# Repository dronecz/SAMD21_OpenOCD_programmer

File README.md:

# SAMD21_OpenOCD_programmer

HW/rev_B - working programmer, buttons & OLED display. SWD header untested.

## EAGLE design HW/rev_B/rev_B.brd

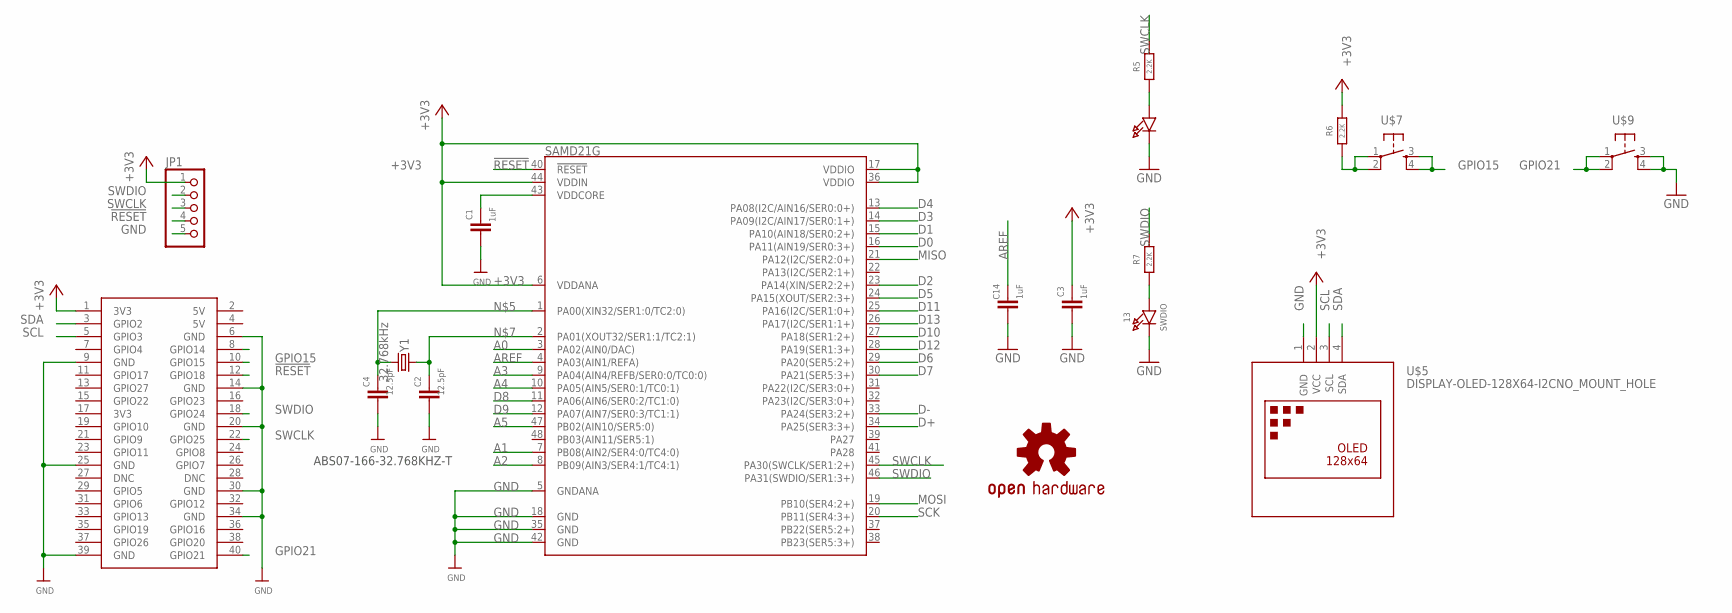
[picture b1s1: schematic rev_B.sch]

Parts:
5: SWCLK; CHIPLED_0805_NOOUTLINE
13: SWDIO; CHIPLED_0805_NOOUTLINE
C1, C3, C14: 1uF; C0805
C2, C4: 12.5pF; C0805
JP1: PINHD-1X5; 1X05
LOGO1: OSHW-LOGOS; OSHW-LOGO-S
R5, R6, R7: 2.2K; R0805
SAMD21G: ATSAMD21G-A; TQFP-48
U$1: RASPBERRY_PI_ZERO
U$5: DISPLAY-OLED-128X64-I2CNO_MOUNT_HOLE; DISPLAY-OLED-128X64-I2C
U$7, U$9: TACTILE_SWITCH_LONG_THT_; TACTILE_SWICTH_THT
Y1: 32.768kHz; CRYSTAL-SMD-3.2X1.5MM

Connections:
!RESET: JP1.4, SAMD21G.40 (!RESET!), U$1.12 (GPIO18)
+3V3: C3.1, JP1.1, R6.1, SAMD21G.6 (VDDANA), SAMD21G.17 (VDDIO), SAMD21G.36 (VDDIO), SAMD21G.44 (VDDIN), U$1.1 (3V3), U$5.2 (VCC)
A0: SAMD21G.3 (PA02(AIN0/DAC))
A1: SAMD21G.7 (PB08(AIN2/SER4:0/TC4:0))
A2: SAMD21G.8 (PB09(AIN3/SER4:1/TC4:1))
A3: SAMD21G.9 (PA04(AIN4/REFB/SER0:0/TC0:0))
A4: SAMD21G.10 (PA05(AIN5/SER0:1/TC0:1))
A5: SAMD21G.47 (PB02(AIN10/SER5:0))
AREF: C14.1, SAMD21G.4 (PA03(AIN1/REFA))
D0: SAMD21G.16 (PA11(AIN19/SER0:3+))
D1: SAMD21G.15 (PA10(AIN18/SER0:2+))
D2: SAMD21G.23 (PA14(XIN/SER2:2+))
D3: SAMD21G.14 (PA09(I2C/AIN17/SER0:1+))
D4: SAMD21G.13 (PA08(I2C/AIN16/SER0:0+))
D5: SAMD21G.24 (PA15(XOUT/SER2:3+))
D6: SAMD21G.29 (PA20(SER5:2+))
D7: SAMD21G.30 (PA21(SER5:3+))
D8: SAMD21G.11 (PA06(AIN6/SER0:2/TC1:0))
D9: SAMD21G.12 (PA07(AIN7/SER0:3/TC1:1))
D10: SAMD21G.27 (PA18(SER1:2+))
D11: SAMD21G.25 (PA16(I2C/SER1:0+))
D12: SAMD21G.28 (PA19(SER1:3+))
D13: SAMD21G.26 (PA17(I2C/SER1:1+))
D+: SAMD21G.34 (PA25(SER3:3+))
D-: SAMD21G.33 (PA24(SER3:2+))
GND: 5.C, 13.C, C1.2, C2.2, C3.2, C4.2, C14.2, JP1.5, SAMD21G.5 (GNDANA), SAMD21G.18 (GND), SAMD21G.35 (GND), SAMD21G.42 (GND), U$1.6 (GND), U$1.9 (GND), U$1.14 (GND), U$1.20 (GND), U$1.25 (GND), U$1.30 (GND), U$1.34 (GND), U$1.39 (GND), U$5.1 (GND), U$9.3, U$9.4
GPIO15: U$1.10 (GPIO15), U$7.3, U$7.4
GPIO21: U$1.40 (GPIO21), U$9.1, U$9.2
MISO: SAMD21G.21 (PA12(I2C/SER2:0+))
MOSI: SAMD21G.19 (PB10(SER4:2+))
unnamed: 13.A, R7.2
unnamed: C4.1, SAMD21G.1 (PA00(XIN32/SER1:0/TC2:0)), Y1.P$2 (2)
unnamed: 5.A, R5.2
unnamed: C2.1, SAMD21G.2 (PA01(XOUT32/SER1:1/TC2:1)), Y1.P$1 (1)
unnamed: R6.2, U$7.1, U$7.2
SCK: SAMD21G.20 (PB11(SER4:3+))
SCL: U$1.5 (GPIO3), U$5.3 (SCL)
SDA: U$1.3 (GPIO2), U$5.4 (SDA)
SWCLK: JP1.3, R5.1, SAMD21G.45 (PA30(SWCLK/SER1:2+)), U$1.22 (GPIO25)
SWDIO: JP1.2, R7.1, SAMD21G.46 (PA31(SWDIO/SER1:3+)), U$1.18 (GPIO24)
VDDCORE: C1.1, SAMD21G.43 (VDDCORE)

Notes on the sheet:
ABS07-166-32.768KHZ-T

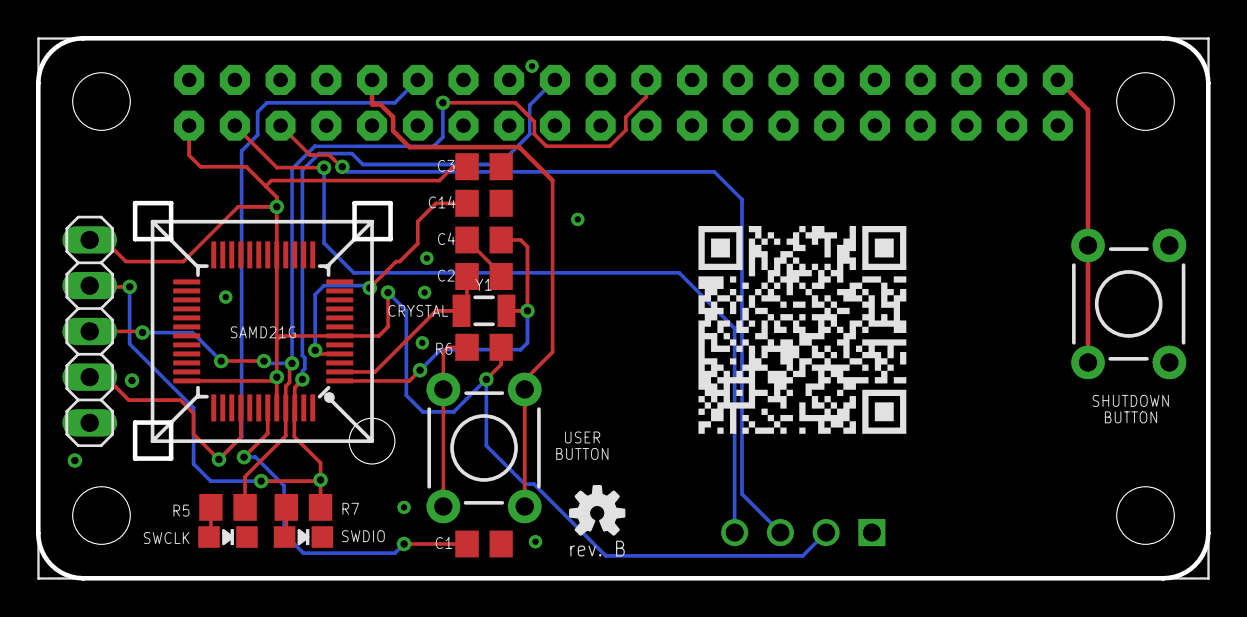
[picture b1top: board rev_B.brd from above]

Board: 2 copper layers, 65.0 x 30.0 mm, 19 parts (1 on the bottom side), 16 nets.

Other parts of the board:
LOGO2: OSHW-LOGOS; OSHW-LOGO-S

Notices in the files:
parts and their libraries:
microbuilder: This work is placed in the public domain, and may be freely used for commercial and non-commercial work with the following conditions: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
SparkFun-Aesthetics: Licensing: Creative Commons ShareAlike 4.0 International - https://creativecommons.org/licenses/by-sa/4.0
